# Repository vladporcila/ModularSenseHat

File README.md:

## This project is licensed under the AGPL, which can be [found here](https://www.gnu.org/licenses/agpl-3.0.en.html).

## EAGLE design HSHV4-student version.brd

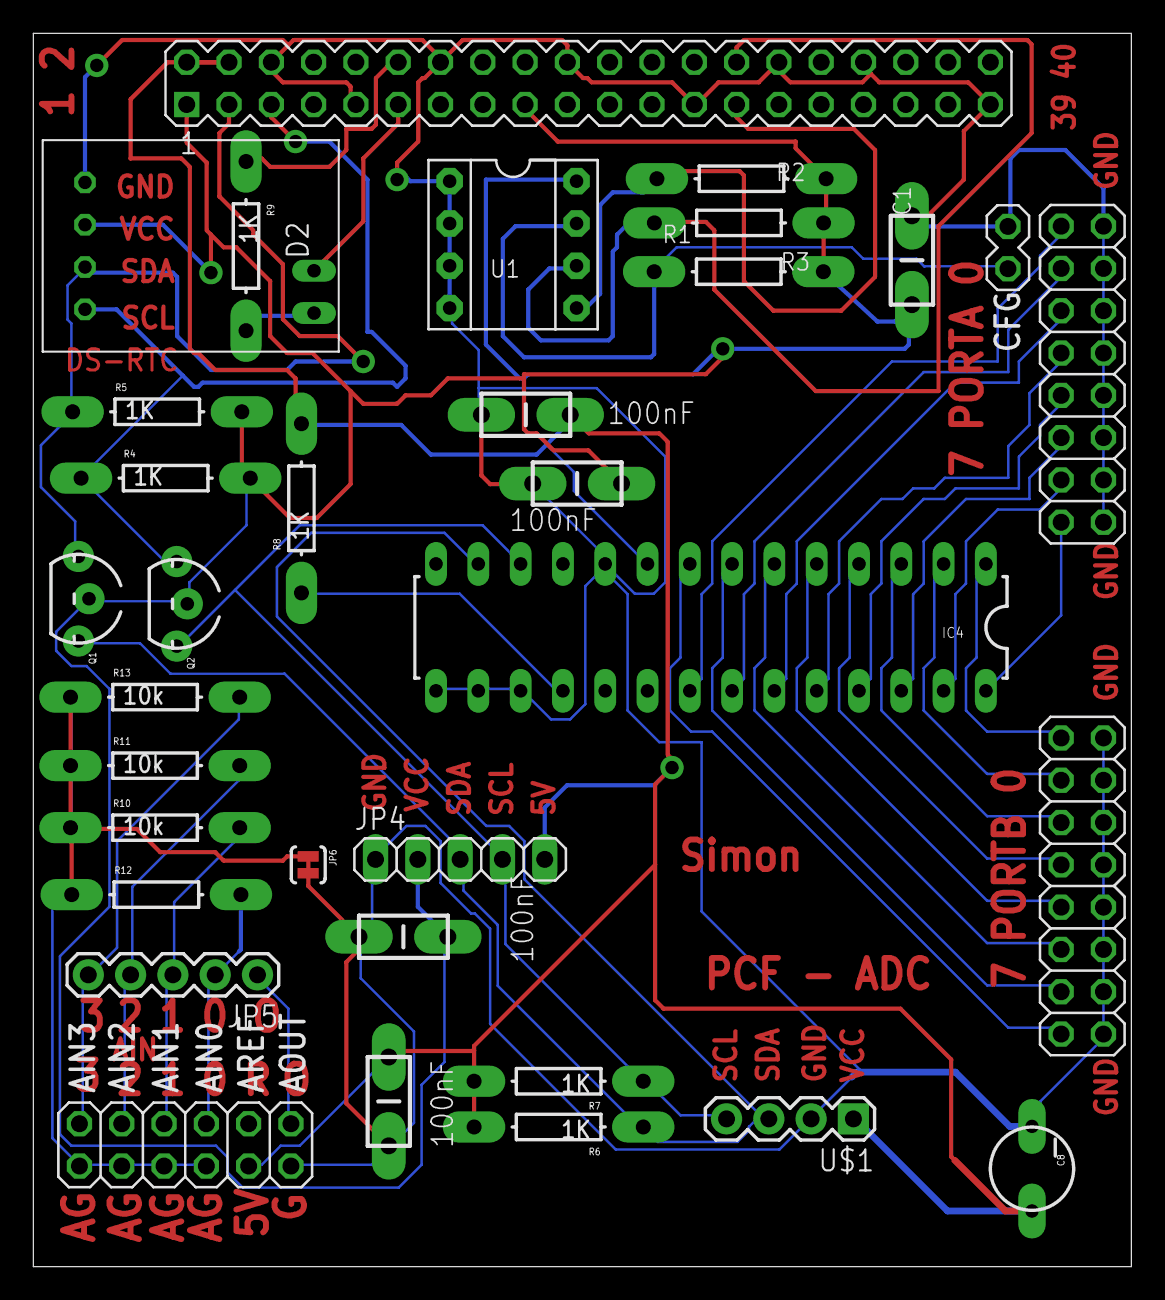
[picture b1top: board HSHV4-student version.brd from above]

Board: 2 copper layers, 65.9 x 74.1 mm, 34 parts (0 on the bottom side), 36 nets.

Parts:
C1, C2, C3, C4, C5: 100nF; CAP-PTH-SMALL-KIT
C8: 10uF; CPOL-RADIAL-10UF-25V
CFG: PIN_W_2
D2: LED3MM-NS
IC1: DS3231; 8PTH
IC4: IO_EXPANDER; DIL28-3
JP1: PORT A; 2X08
JP2: PORT B; 2X08
JP3: 2X06
JP4, JP5: 1X05
JP6: JUMPER-PAD-2-NC_BY_TRACE; PAD-JUMPER-2-NC_BY_TRACE_YES_SILK
K1: PIN20X2; PIN_20X2
Q1, Q2: MOSFET-NCHANNEL2N7000; TO-92
R1, R2, R3, R4, R5, R6, R7, R8, R9: 1K; AXIAL-0.3
R10, R11, R12, R13: 10k; AXIAL-0.3
U1: 256K_EEPROM; DIL08
U$1: PCF8591; 1X04

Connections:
+3V3: C1.1, C2.1, C4.2, IC1.2, JP4.2, K1.1, K1.17, Q1.2, Q2.2, R1.P$2, R2.P$2, R3.P$2, R4.P$2, R5.P$2, U1.8
+5V: C3.1, C5.2, C8.1, IC4.9, JP3.9, JP4.5, K1.2, K1.4, R6.P$2, R7.P$2, R8.P$2, U$1.1
AGND: JP3.1, JP3.3, JP3.5, JP3.7, JP6.1, R10.P$1, R11.P$1, R12.P$1, R13.P$1
AIN0: JP3.8, JP5.2, R12.P$2
AIN1: JP3.6, JP5.3, R10.P$2
AIN2: JP3.4, JP5.4, R11.P$2
AIN3: JP3.2, JP5.5, R13.P$2
GND: C1.2, C2.2, C3.2, C4.1, C5.1, C8.2, CFG.2, IC1.1, IC4.10, IC4.15, IC4.16, IC4.17, JP1.2, JP1.4, JP1.6, JP1.8, JP1.10, JP1.12, JP1.14, JP1.16, JP2.2, JP2.4, JP2.6, JP2.8, JP2.10, JP2.12, JP2.14, JP2.16, JP3.11, JP4.1, JP6.2, K1.6, K1.9, K1.14, K1.20, K1.25, K1.30, K1.34, K1.39, U1.1, U1.2, U1.3, U1.4, U$1.2
GPIO17: D2.K, K1.11
GPIO18: K1.12, R9.P$1
unnamed: JP3.12, JP5.1
unnamed: D2.A, R9.P$2
unnamed: CFG.1, R3.P$1, U1.7
unnamed: IC4.21, JP1.1
unnamed: IC4.22, JP1.3
unnamed: IC4.18, R8.P$1
unnamed: IC4.23, JP1.5
unnamed: IC4.24, JP1.7
unnamed: IC4.25, JP1.9
unnamed: IC4.26, JP1.11
unnamed: IC4.27, JP1.13
unnamed: IC4.28, JP1.15
unnamed: IC4.1, JP2.1
unnamed: IC4.2, JP2.3
unnamed: IC4.3, JP2.5
unnamed: IC4.4, JP2.7
unnamed: IC4.5, JP2.9
unnamed: IC4.6, JP2.11
unnamed: IC4.7, JP2.13
unnamed: IC4.8, JP2.15
SCL0-3: K1.28, R1.P$1, U1.6
SCL1-3: IC1.4, K1.5, Q2.1, R4.P$1
SCL1-5: IC4.12, JP4.4, Q2.3, R7.P$1, U$1.4
SDA0-3: K1.27, R2.P$1, U1.5
SDA1-3: IC1.3, K1.3, Q1.1, R5.P$1
SDA1-5: IC4.13, JP4.3, Q1.3, R6.P$1, U$1.3

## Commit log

2016-06-22 Added board and BOM
2016-06-22 Added reference to AGPL license
2016-06-22 Fixed link
2016-07-07 Increased size of via's for easier soldering
2016-08-15 Made larger pads

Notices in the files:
parts and their libraries:
SparkFun-Connectors: Licensing: Creative Commons ShareAlike 4.0 International - https://creativecommons.org/licenses/by-sa/4.0
